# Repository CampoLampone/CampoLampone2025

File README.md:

# CampoLampone2025
This is repo for Firmware, PCBs, Images, schemes and stuff

## Setup

1) Clone with all the submodules
```
	git clone <repository-name-ssh-or-https> --recursive
```

2) Add TinyUSB to SDK
```
	cd pico-sdk && git submodule update --init
```

3) Create build dir and build da project!
```
	mkdir build && cd build
	cmake ..
	make -j<number of jobs>
```

## TODO

- [ ] Check when to move from pico-sdk develop branch to main branch

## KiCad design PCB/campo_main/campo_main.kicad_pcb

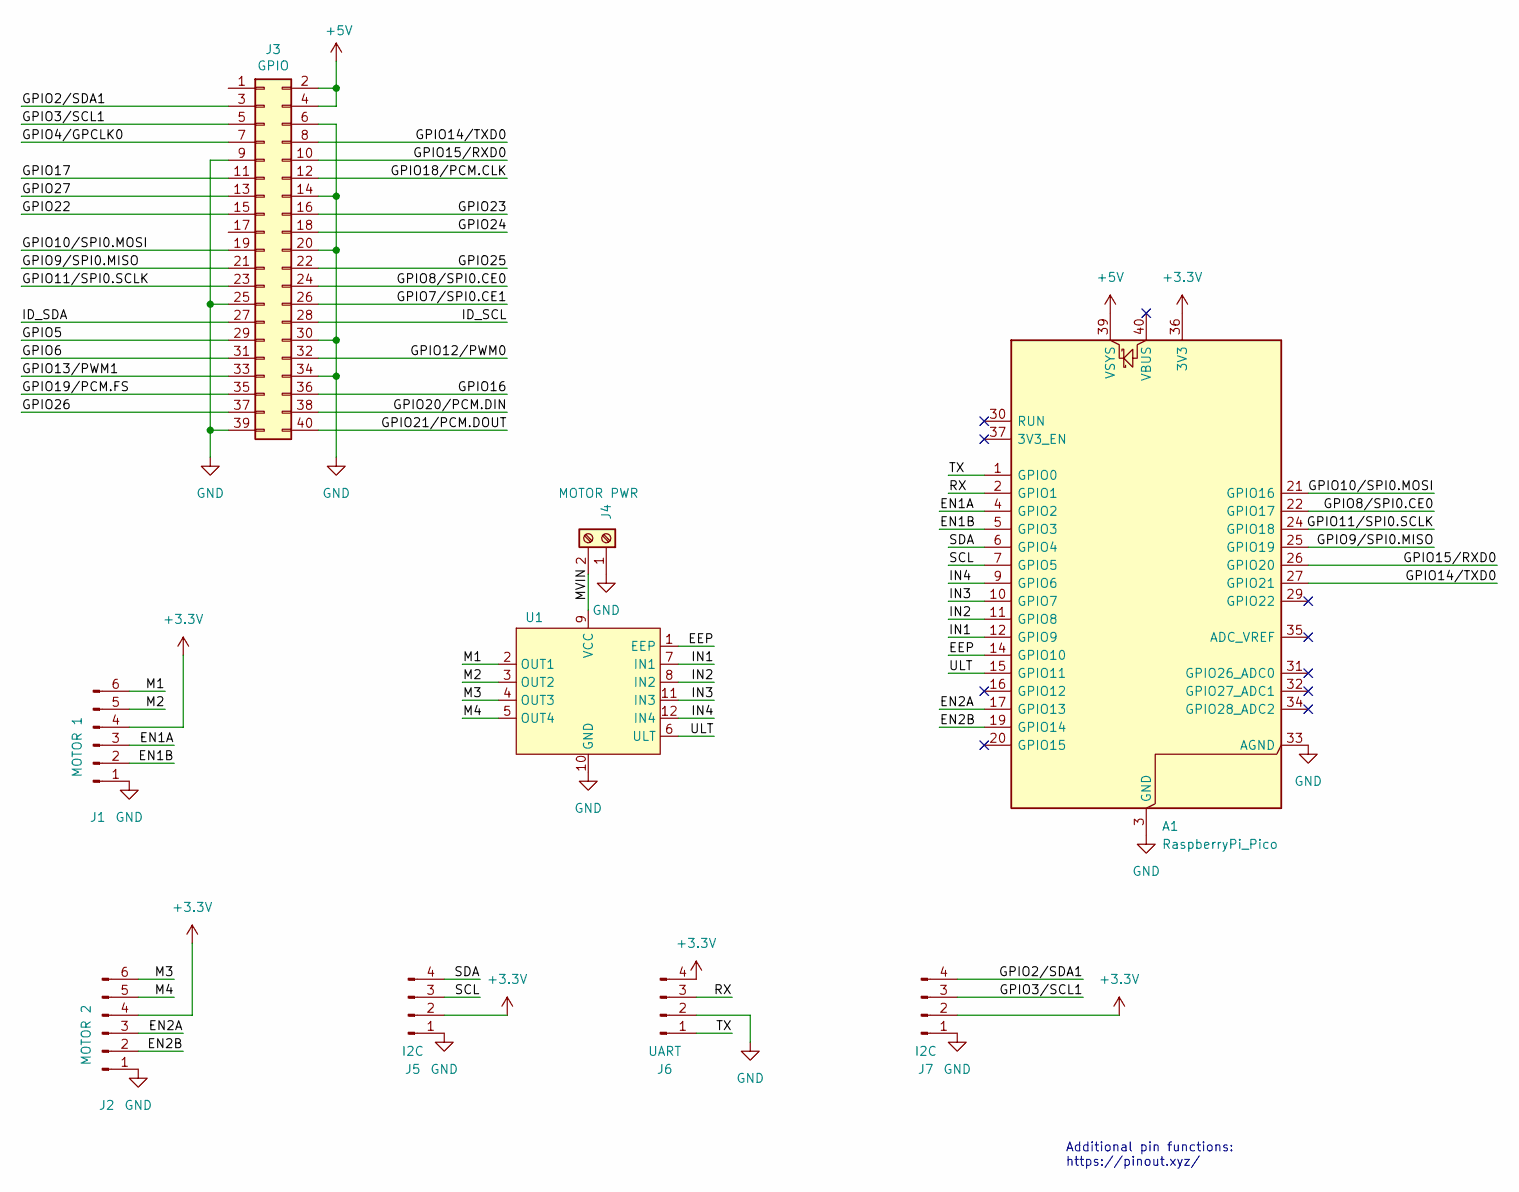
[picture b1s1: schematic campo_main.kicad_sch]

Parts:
A1: RaspberryPi_Pico; RaspberryPi_Pico_Common_Unspecified
J1: MOTOR 1; PinHeader_1x06_P2.54mm_Vertical
J2: MOTOR 2; PinHeader_1x06_P2.54mm_Vertical
J3: GPIO; PinSocket_2x20_P2.54mm_Vertical
J4: MOTOR PWR; TerminalBlock_4Ucon_1x02_P3.50mm_Horizontal
J5, J7: I2C; PinHeader_1x04_P2.54mm_Vertical
J6: UART; PinHeader_1x04_P2.54mm_Vertical
U1: DRV8833

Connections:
+3.3V: A1.36 (3V3), J1.4, J2.4, J5.2, J6.4, J7.2
+5V: A1.39 (VSYS), J3.2, J3.4
/EEP: A1.14 (GPIO10), U1.1 (EEP)
/EN1A: A1.4 (GPIO2), J1.3
/EN1B: A1.5 (GPIO3), J1.2
/EN2A: A1.17 (GPIO13), J2.3
/EN2B: A1.19 (GPIO14), J2.2
/GPIO2/SDA1: J3.3, J7.4
/GPIO3/SCL1: J3.5, J7.3
/GPIO4/GPCLK0: J3.7
/GPIO5: J3.29
/GPIO6: J3.31
/GPIO7/SPI0.CE1: J3.26
/GPIO8/SPI0.CE0: A1.22 (GPIO17), J3.24
/GPIO9/SPI0.MISO: A1.25 (GPIO19), J3.21
/GPIO10/SPI0.MOSI: A1.21 (GPIO16), J3.19
/GPIO11/SPI0.SCLK: A1.24 (GPIO18), J3.23
/GPIO12/PWM0: J3.32
/GPIO13/PWM1: J3.33
/GPIO14/TXD0: A1.27 (GPIO21), J3.8
/GPIO15/RXD0: A1.26 (GPIO20), J3.10
/GPIO16: J3.36
/GPIO17: J3.11
/GPIO18/PCM.CLK: J3.12
/GPIO19/PCM.FS: J3.35
/GPIO20/PCM.DIN: J3.38
/GPIO21/PCM.DOUT: J3.40
/GPIO22: J3.15
/GPIO23: J3.16
/GPIO24: J3.18
/GPIO25: J3.22
/GPIO26: J3.37
/GPIO27: J3.13
/ID_SCL: J3.28
/ID_SDA: J3.27
/IN1: A1.12 (GPIO9), U1.7 (IN1)
/IN2: A1.11 (GPIO8), U1.8 (IN2)
/IN3: A1.10 (GPIO7), U1.11 (IN3)
/IN4: A1.9 (GPIO6), U1.12 (IN4)
/M1: J1.6, U1.2 (OUT1)
/M2: J1.5, U1.3 (OUT2)
/M3: J2.6, U1.4 (OUT3)
/M4: J2.5, U1.5 (OUT4)
/MVIN: J4.2, U1.9 (VCC)
/RX: A1.2 (GPIO1), J6.3
/SCL: A1.7 (GPIO5), J5.3
/SDA: A1.6 (GPIO4), J5.4
/TX: A1.1 (GPIO0), J6.1
/ULT: A1.15 (GPIO11), U1.6 (ULT)
GND: A1.3 (GND), A1.8 (GND), A1.13 (GND), A1.18 (GND), A1.23 (GND), A1.28 (GND), A1.33 (AGND), A1.38 (GND), J1.1, J2.1, J3.6, J3.9, J3.14, J3.20, J3.25, J3.30, J3.34, J3.39, J4.1, J5.1, J6.2, J7.1, U1.10 (GND)

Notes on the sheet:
Additional pin functions: https://pinout.xyz/

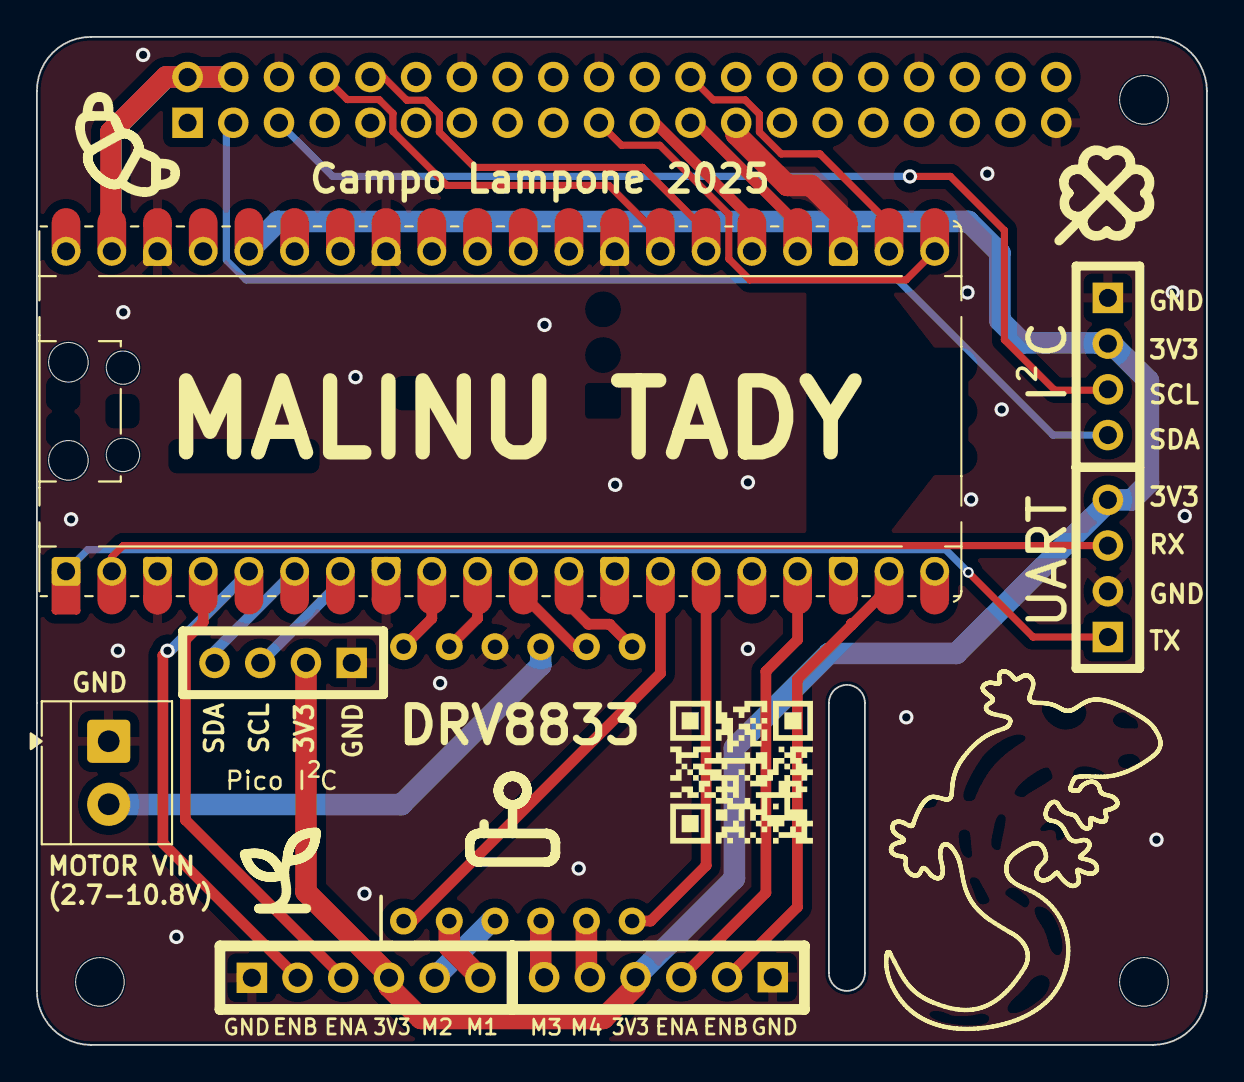
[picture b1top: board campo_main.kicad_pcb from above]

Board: 2 copper layers, 65.0 x 56.0 mm, 12 parts (1 on the bottom side), 30 nets.

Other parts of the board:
MH2, MH3, MH4: MountingHole_2.7mm_M2.5

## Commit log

2025-07-08 Some PCB work around
2025-07-08 Update schematic
2025-07-09 PCB update
2025-07-09 Added assets for PCB
2025-07-09 Upgrade silkscreen
2025-07-09 Fix broken traces
2025-07-09 Fix for PCB
2025-07-10 Some PCB Changes
2025-07-10 Added some assets needed to PCB
2025-07-11 PCB final
2025-07-12 Implemented motor pwm control, encoder read and pid speed control
2025-07-15 added some instructions + added pico-sdk/develop as submodule
2025-07-31 Removed pico-sdk submodule
2025-07-31 Playing with PID
2025-08-07 Some small fixes
2025-08-07 Use global arch sdk
2025-08-07 Hard-fixed motors and encoders
2025-08-07 Improved motors driver
2025-08-07 [MERGE] Added substep encoder, it sexy, but I don't understand yet...
2025-08-09 Fixed recomputation to RPM
2025-08-10 Cleaned up project structure, removed typo
2025-08-10 SPI works!
2025-08-11 Speed controler clean up
2025-08-11 some small changes
2025-08-11 [Merge] Some directional fixes
2025-08-11 Some improvements, added brake and coast cmd
2025-08-11 Speed controler fix
2025-08-11 Tests fix
2025-08-11 Fixed encoders in tests
2025-08-15 Add traffic light infrastructure
    A React frontend for configuring the traffic lights
    with a FastAPI backend all packed in Docker
    Docker compose for painless deploying
    Micropython code for the ESPs (you could probably use Pico Ws) that
    control the actual LEDs
2025-08-15 Clearing pid cache when sets new target value
2025-08-17 Small fixes
2025-08-17 Added emergence stop, when motors stall
2025-08-17 Added anti windup for integral in speed controller
2025-08-18 Small typo 😅
2025-08-18 Repaired emergency stop (hopefully)
2025-08-18 Added estop reset to SPI commands
2025-08-18 Removed anti windup
2025-08-18 Forgot something...
2025-08-18 WIP: Added SSD1306 code (not implemented correctly yet)
2025-08-19 Made display working and some naming changes
2025-08-19 Some fixes and stuf 👲
2025-08-19 Added clear to ssd1306_draw_struct
2025-08-19 Repaired speed printing on display
2025-08-19 Added chacking for Display connection
2025-08-19 Added Setting hostname via SPI 🧚
2025-08-19 Aligned RPM values on display
2025-08-21 Small Pid shit 🪥
2025-08-22 Added low pass filter
2025-11-16 Add a README for Traffic lights
